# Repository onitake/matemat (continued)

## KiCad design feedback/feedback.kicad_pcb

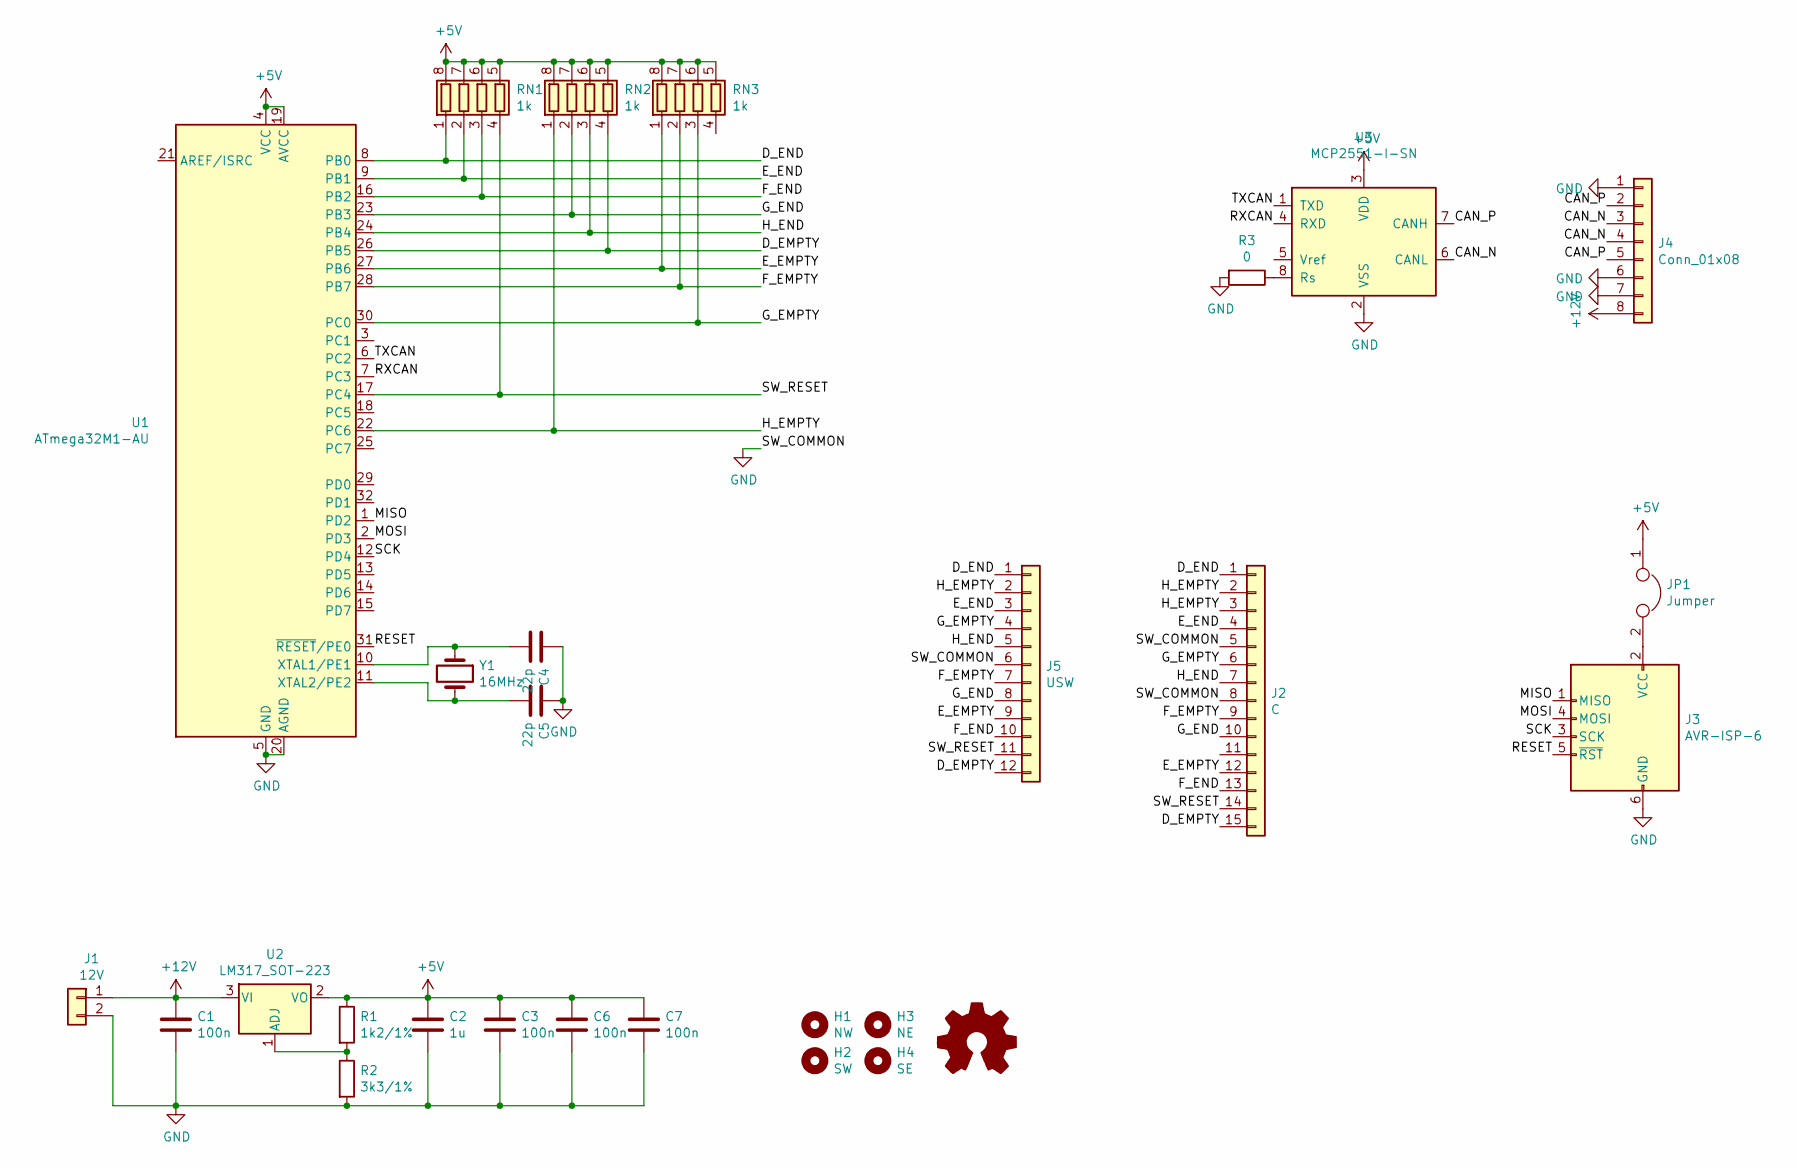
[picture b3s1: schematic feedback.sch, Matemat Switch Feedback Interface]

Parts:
C1, C3, C6, C7: 100n; C_0805_2012Metric_Pad1.15x1.40mm_HandSolder
C2: 1u; C_0805_2012Metric_Pad1.15x1.40mm_HandSolder
C4, C5: 22p; C_0805_2012Metric_Pad1.15x1.40mm_HandSolder
H1: NW; MountingHole_3.2mm_M3_ISO7380
H2: SW; MountingHole_3.2mm_M3_ISO7380
H3: NE; MountingHole_3.2mm_M3_ISO7380
H4: SE; MountingHole_3.2mm_M3_ISO7380
J1: 12V; TerminalBlock_TE_282834-2_1x02_P2.54mm_Horizontal
J2: C; Molex_MLX-42002_10-84-4150_3x5-Pin_P6.35mm_Vertical
J3: AVR-ISP-6; PinHeader_2x03_P2.54mm_Vertical
J4: Conn_01x08; TerminalBlock_TE_282834-8_1x08_P2.54mm_Horizontal
J5: USW; TerminalBlock_TE_1-282834-2_1x12_P2.54mm_Horizontal
JP1: Jumper; PinHeader_1x02_P2.54mm_Vertical
OHW1: Logo_Open_Hardware_Small; OSHW-Logo2_7.3x6mm_SilkScreen
R1: 1k2/1%; R_0805_2012Metric_Pad1.15x1.40mm_HandSolder
R2: 3k3/1%; R_0805_2012Metric_Pad1.15x1.40mm_HandSolder
R3: 0; R_0805_2012Metric_Pad1.15x1.40mm_HandSolder
RN1, RN2, RN3: 1k; R_Array_Convex_4x1206
U1: ATmega32M1-AU; TQFP-32_7x7mm_P0.8mm
U2: LM317_SOT-223; SOT-223-3_TabPin2
U3: MCP2551-I-SN; SOIC-8_3.9x4.9mm_P1.27mm
Y1: 16MHz; Crystal_SMD_HC49-SD

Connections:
+5V: C2.1, C3.1, C6.1, C7.1, JP1.1, R1.1, RN1.5 (R4.2), RN1.6 (R3.2), RN1.7 (R2.2), RN1.8 (R1.2), RN2.5 (R4.2), RN2.6 (R3.2), RN2.7 (R2.2), RN2.8 (R1.2), RN3.5 (R4.2), RN3.6 (R3.2), RN3.7 (R2.2), RN3.8 (R1.2), U1.4 (VCC), U1.19 (AVCC), U2.2 (VO), U3.3 (VDD)
+12V: C1.1, J1.1, J4.8, U2.3 (VI)
/CAN_N: J4.3, J4.4, U3.6 (CANL)
/CAN_P: J4.2, J4.5, U3.7 (CANH)
/D_EMPTY: J2.15, J5.12, RN2.4 (R4.1), U1.26 (PB5)
/D_END: J2.1, J5.1, RN1.1 (R1.1), U1.8 (PB0)
/E_EMPTY: J2.12, J5.9, RN3.1 (R1.1), U1.27 (PB6)
/E_END: J2.4, J5.3, RN1.2 (R2.1), U1.9 (PB1)
/F_EMPTY: J2.9, J5.7, RN3.2 (R2.1), U1.28 (PB7)
/F_END: J2.13, J5.10, RN1.3 (R3.1), U1.16 (PB2)
/G_EMPTY: J2.6, J5.4, RN3.3 (R3.1), U1.30 (PC0)
/G_END: J2.10, J5.8, RN2.2 (R2.1), U1.23 (PB3)
/H_EMPTY: J2.2, J2.3, J5.2, RN2.1 (R1.1), U1.22 (PC6)
/H_END: J2.7, J5.5, RN2.3 (R3.1), U1.24 (PB4)
/MISO: J3.1 (MISO), U1.1 (PD2)
/MOSI: J3.4 (MOSI), U1.2 (PD3)
/RESET: J3.5 (~RST), U1.31 (~RESET~/PE0)
/RXCAN: U1.7 (PC3), U3.4 (RXD)
/SCK: J3.3 (SCK), U1.12 (PD4)
/SW_RESET: J2.14, J5.11, RN1.4 (R4.1), U1.17 (PC4)
/TXCAN: U1.6 (PC2), U3.1 (TXD)
GND: C1.2, C2.2, C3.2, C4.1, C5.1, C6.2, C7.2, J1.2, J2.5, J2.8, J3.6 (GND), J4.1, J4.6, J4.7, J5.6, R2.2, R3.2, U1.5 (GND), U1.20 (AGND), U3.2 (VSS)
unnamed: C4.2, U1.10 (XTAL1/PE1), Y1.1
unnamed: C5.2, U1.11 (XTAL2/PE2), Y1.2
unnamed: J3.2 (VCC), JP1.2
unnamed: R1.2, R2.1, U2.1 (ADJ)
unnamed: R3.1, U3.8 (Rs)

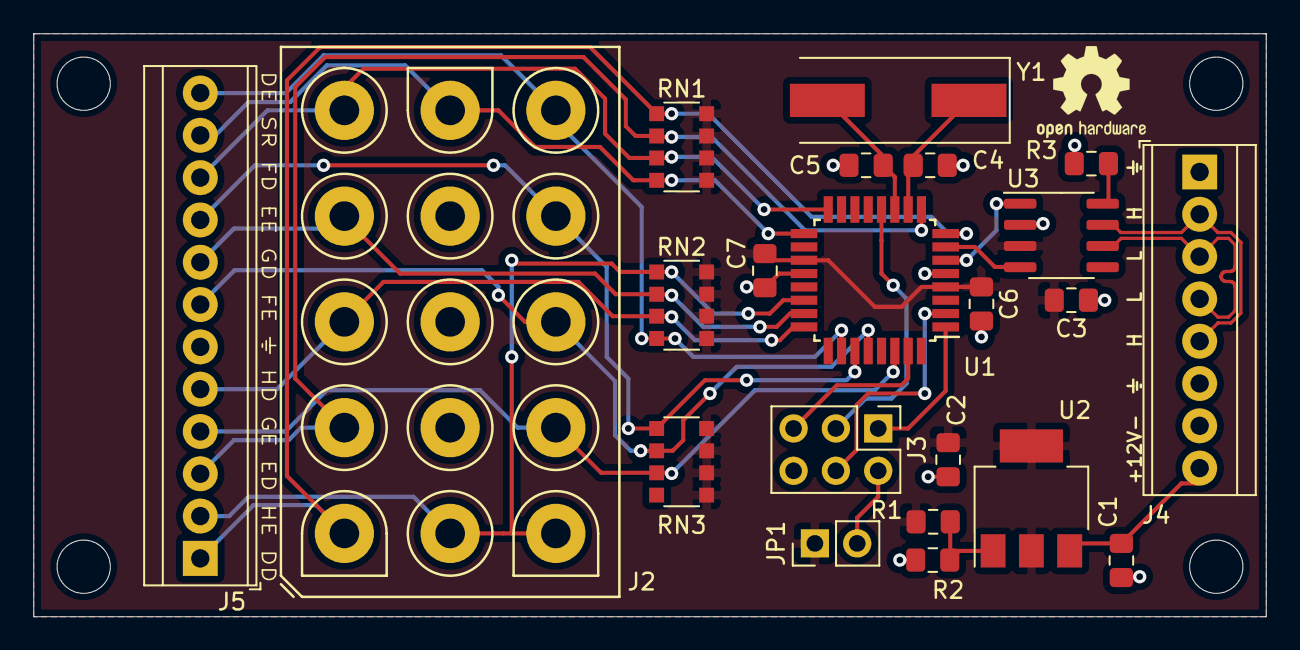
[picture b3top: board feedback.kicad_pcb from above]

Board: 2 copper layers, 74.0 x 35.0 mm, 27 parts (0 on the bottom side), 27 nets.

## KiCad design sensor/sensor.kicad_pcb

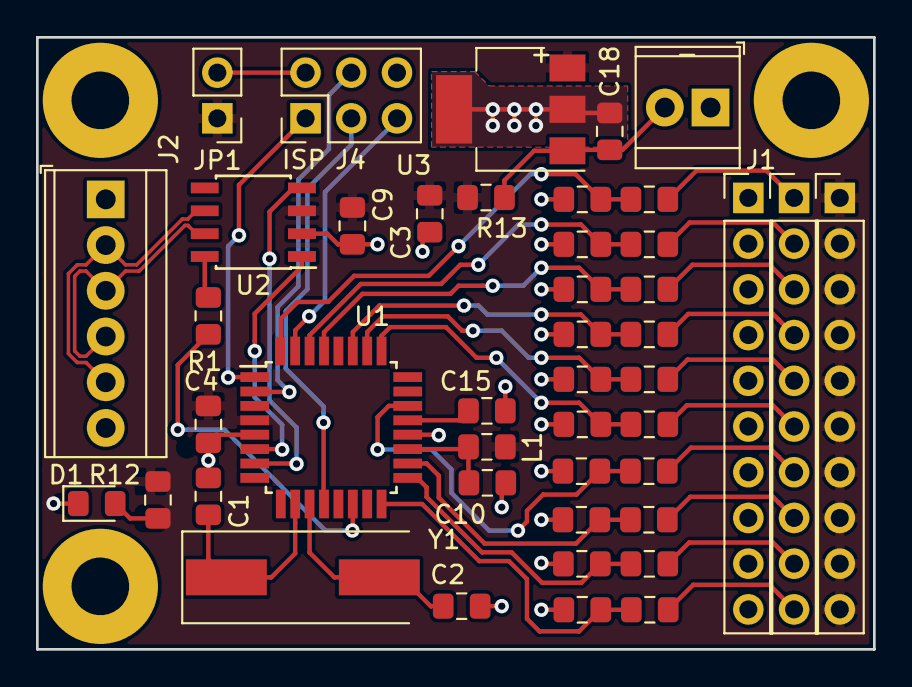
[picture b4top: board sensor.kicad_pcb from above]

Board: 2 copper layers, 46.5 x 34.0 mm, 47 parts (0 on the bottom side), 39 nets.

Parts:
C1, C2: 22p; C_0805_2012Metric_Pad1.15x1.40mm_HandSolder
C3: 10u; C_0805_2012Metric_Pad1.15x1.40mm_HandSolder
C4, C9, C10, C18: 100n; C_0805_2012Metric_Pad1.15x1.40mm_HandSolder
C5, C6, C7, C8, C11, C12, C13, C14, C16, C17: 10n; C_0805_2012Metric_Pad1.15x1.40mm_HandSolder
C15: 100n/0R; C_0805_2012Metric_Pad1.15x1.40mm_HandSolder
D1: POWER; LED_0805_2012Metric_Pad1.15x1.40mm_HandSolder
H1: NW; MountingHole_3.2mm_M3_Pad
H2: NE; MountingHole_3.2mm_M3_Pad
H3: SW; MountingHole_3.2mm_M3_Pad
J1: 12V; TerminalBlock_TE_282834-2_1x02_P2.54mm_Horizontal
J2: CAN; TerminalBlock_TE_282834-6_1x06_P2.54mm_Horizontal
J4: AVR-ISP-6; PinHeader_2x03_P2.54mm_Vertical
J5: SENSOR IN; PinHeader_1x10_P2.54mm_Vertical
J6: SENSOR VCC; PinHeader_1x10_P2.54mm_Vertical
J7: SENSOR GND; PinHeader_1x10_P2.54mm_Vertical
JP1: ISP POWER; PinHeader_1x02_P2.54mm_Vertical
L1: 10u; L_0805_2012Metric_Pad1.15x1.40mm_HandSolder
R1, R2, R3, R4, R5, R6, R7, R8, R9, R10, R11: 0; R_0805_2012Metric_Pad1.15x1.40mm_HandSolder
R12: 470; R_0805_2012Metric_Pad1.15x1.40mm_HandSolder
R13: DNP/0; R_0805_2012Metric_Pad1.15x1.40mm_HandSolder
U1: ATmega32M1-AU; TQFP-32_7x7mm_P0.8mm
U2: MCP2551-I-SN; SOIC-8_3.9x4.9mm_P1.27mm
U3: LM2937xMP; SOT-223-3_TabPin2
Y1: 16MHz; Crystal_SMD_HC49-SD

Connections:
/ADC5: C8.1, R5.2, U1.16
/ADC8: C7.1, R4.2, U1.17
/ADC9: C6.1, R3.2, U1.18
/ADC10: C5.1, R2.2, U1.22
/AIN0: J5.7, R2.1
/AIN1: J5.8, R3.1
/AIN2: J5.9, R4.1
/AIN3: J5.10, R5.1
/AREF: C15.1, U1.21
/CAN_HISPEED: R1.2, U1.14
/CAN_N: J2.2, J2.5, U2.6
/CAN_P: J2.3, J2.4, U2.7
/CAN_RXD: U1.7, U2.4
/CAN_TXD: U1.6, U2.1
/DIN0: J5.1, R6.1
/DIN1: J5.2, R7.1
/DIN2: J5.3, R8.1
/DIN3: J5.4, R9.1
/DIN4: J5.5, R10.1
/DIN5: J5.6, R11.1
/ISP_MISO: J4.1, U1.1
/ISP_MOSI: J4.4, U1.2
/ISP_SCK: J4.3, U1.12
/PCINT5: C16.1, R10.2, U1.26
/PCINT6: C14.1, R9.2, U1.27
/PCINT8: C12.1, R7.2, U1.30
/PCINT15: C17.1, R11.2, U1.25
/PCINT16: C13.1, R8.2, U1.29
/PCINT17: C11.1, R6.2, U1.32
/~ISP_RESET: J4.5, U1.31
GND: C1.2, C2.1, C3.2, C4.2, C5.2, C6.2, C7.2, C8.2, C9.2, C10.2, C11.2, C12.2, C13.2, C14.2, C15.2, C16.2, C17.2, C18.2, D1.1, H1.1, H2.1, H3.1, J1.1, J2.1, J2.6, J4.6, J7.1, J7.2, J7.3, J7.4, J7.5, J7.6, J7.7, J7.8, J7.9, J7.10, U1.5, U1.20, U2.2, U3.2
unnamed: C1.1, U1.10, Y1.1
unnamed: C2.2, U1.11, Y1.2
unnamed: C18.1, J1.2, R13.2, U3.1
unnamed: D1.2, R12.1
unnamed: J4.2, JP1.2
unnamed: R1.1, U2.8
VAA: C10.1, L1.2, U1.19
VCC: C3.1, C4.1, C9.1, J6.1, J6.2, J6.3, J6.4, J6.5, J6.6, J6.7, J6.8, J6.9, J6.10, JP1.1, L1.1, R12.2, R13.1, U1.4, U2.3, U3.3

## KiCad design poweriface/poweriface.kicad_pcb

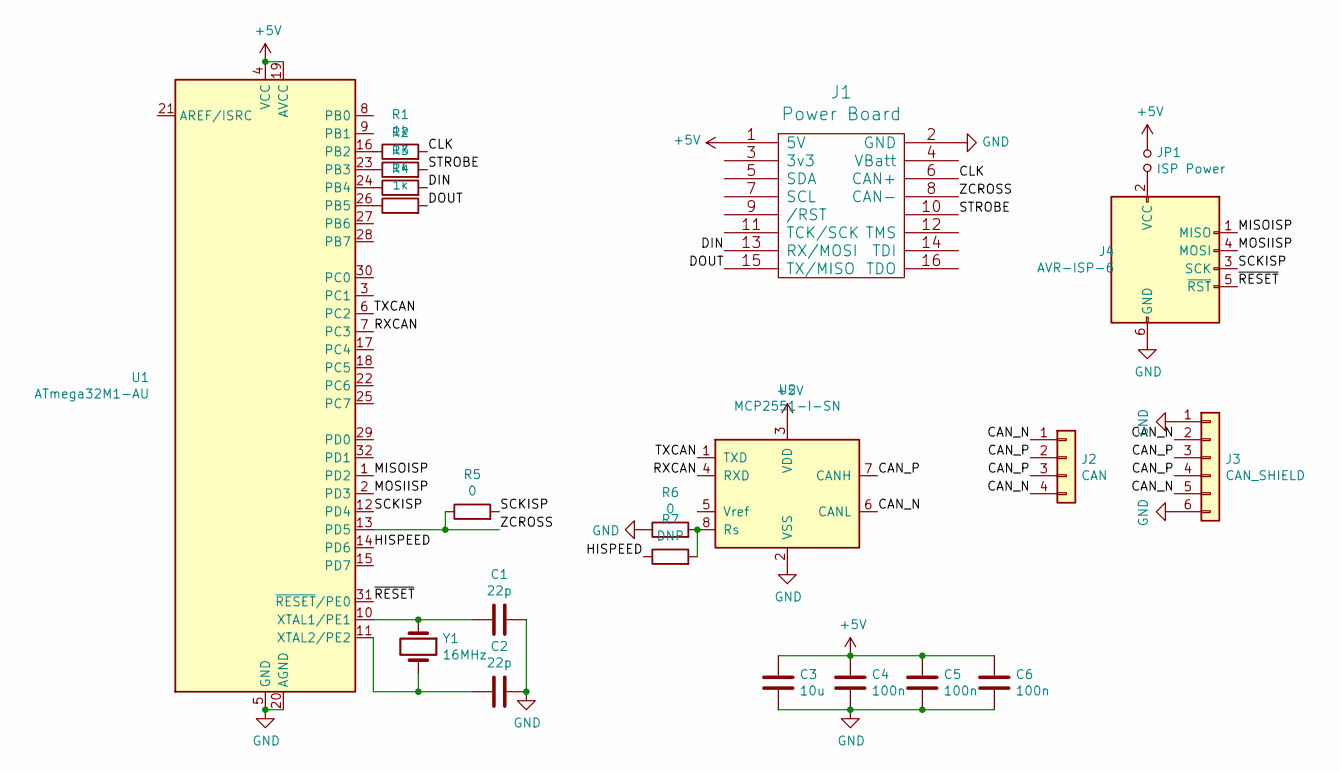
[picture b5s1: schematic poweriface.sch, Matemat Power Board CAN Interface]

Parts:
C1, C2: 22p; C_0805_2012Metric_Pad1.15x1.40mm_HandSolder
C3: 10u; C_0805_2012Metric_Pad1.15x1.40mm_HandSolder
C4, C5, C6: 100n; C_0805_2012Metric_Pad1.15x1.40mm_HandSolder
J1: Power Board; PinSocket_2x08_P2.54mm_Vertical
J2: CAN; TerminalBlock_TE_282834-4_1x04_P2.54mm_Horizontal
J3: CAN_SHIELD; TerminalBlock_TE_282834-6_1x06_P2.54mm_Horizontal
J4: AVR-ISP-6; PinHeader_2x03_P2.54mm_Vertical
JP1: ISP Power; PinHeader_1x02_P2.54mm_Vertical
R1, R2, R3, R4: 1k; R_0805_2012Metric_Pad1.15x1.40mm_HandSolder
R5, R6: 0; R_0805_2012Metric_Pad1.15x1.40mm_HandSolder
R7: DNP; R_0805_2012Metric_Pad1.15x1.40mm_HandSolder
U1: ATmega32M1-AU; TQFP-32_7x7mm_P0.8mm
U2: MCP2551-I-SN; SOIC-8_3.9x4.9mm_P1.27mm
Y1: 16MHz; Crystal_SMD_HC49-SD

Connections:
+5V: C3.1, C4.1, C5.1, C6.1, J1.1 (5V), JP1.1, U1.4 (VCC), U1.19 (AVCC), U2.3 (VDD)
/CAN_N: J2.1, J2.4, J3.2, J3.5, U2.6 (CANL)
/CAN_P: J2.2, J2.3, J3.3, J3.4, U2.7 (CANH)
/CLK: J1.6 (CAN+), R1.2
/DIN: J1.13 (RX/MOSI), R3.2
/DOUT: J1.15 (TX/MISO), R4.2
/HISPEED: R7.1, U1.14 (PD6)
/MISOISP: J4.1 (MISO), U1.1 (PD2)
/MOSIISP: J4.4 (MOSI), U1.2 (PD3)
/RXCAN: U1.7 (PC3), U2.4 (RXD)
/SCKISP: J4.3 (SCK), R5.2, U1.12 (PD4)
/STROBE: J1.10, R2.2
/TXCAN: U1.6 (PC2), U2.1 (TXD)
/ZCROSS: J1.8 (CAN-), R5.1, U1.13 (PD5)
/~RESET: J4.5 (~RST), U1.31 (~RESET~/PE0)
GND: C1.1, C2.1, C3.2, C4.2, C5.2, C6.2, J1.2 (GND), J3.1, J3.6, J4.6 (GND), R6.1, U1.5 (GND), U1.20 (AGND), U2.2 (VSS)
unnamed: C1.2, U1.10 (XTAL1/PE1), Y1.1
unnamed: C2.2, U1.11 (XTAL2/PE2), Y1.2
unnamed: J4.2 (VCC), JP1.2
unnamed: R1.1, U1.16 (PB2)
unnamed: R2.1, U1.23 (PB3)
unnamed: R3.1, U1.24 (PB4)
unnamed: R4.1, U1.26 (PB5)
unnamed: R6.2, R7.2, U2.8 (Rs)

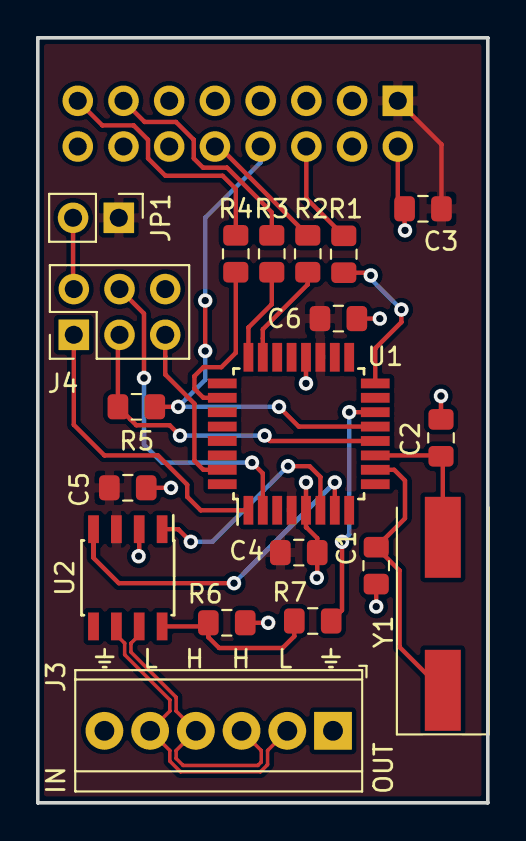
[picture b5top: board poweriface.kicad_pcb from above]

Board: 2 copper layers, 25.0 x 42.5 mm, 20 parts (1 on the bottom side), 24 nets.

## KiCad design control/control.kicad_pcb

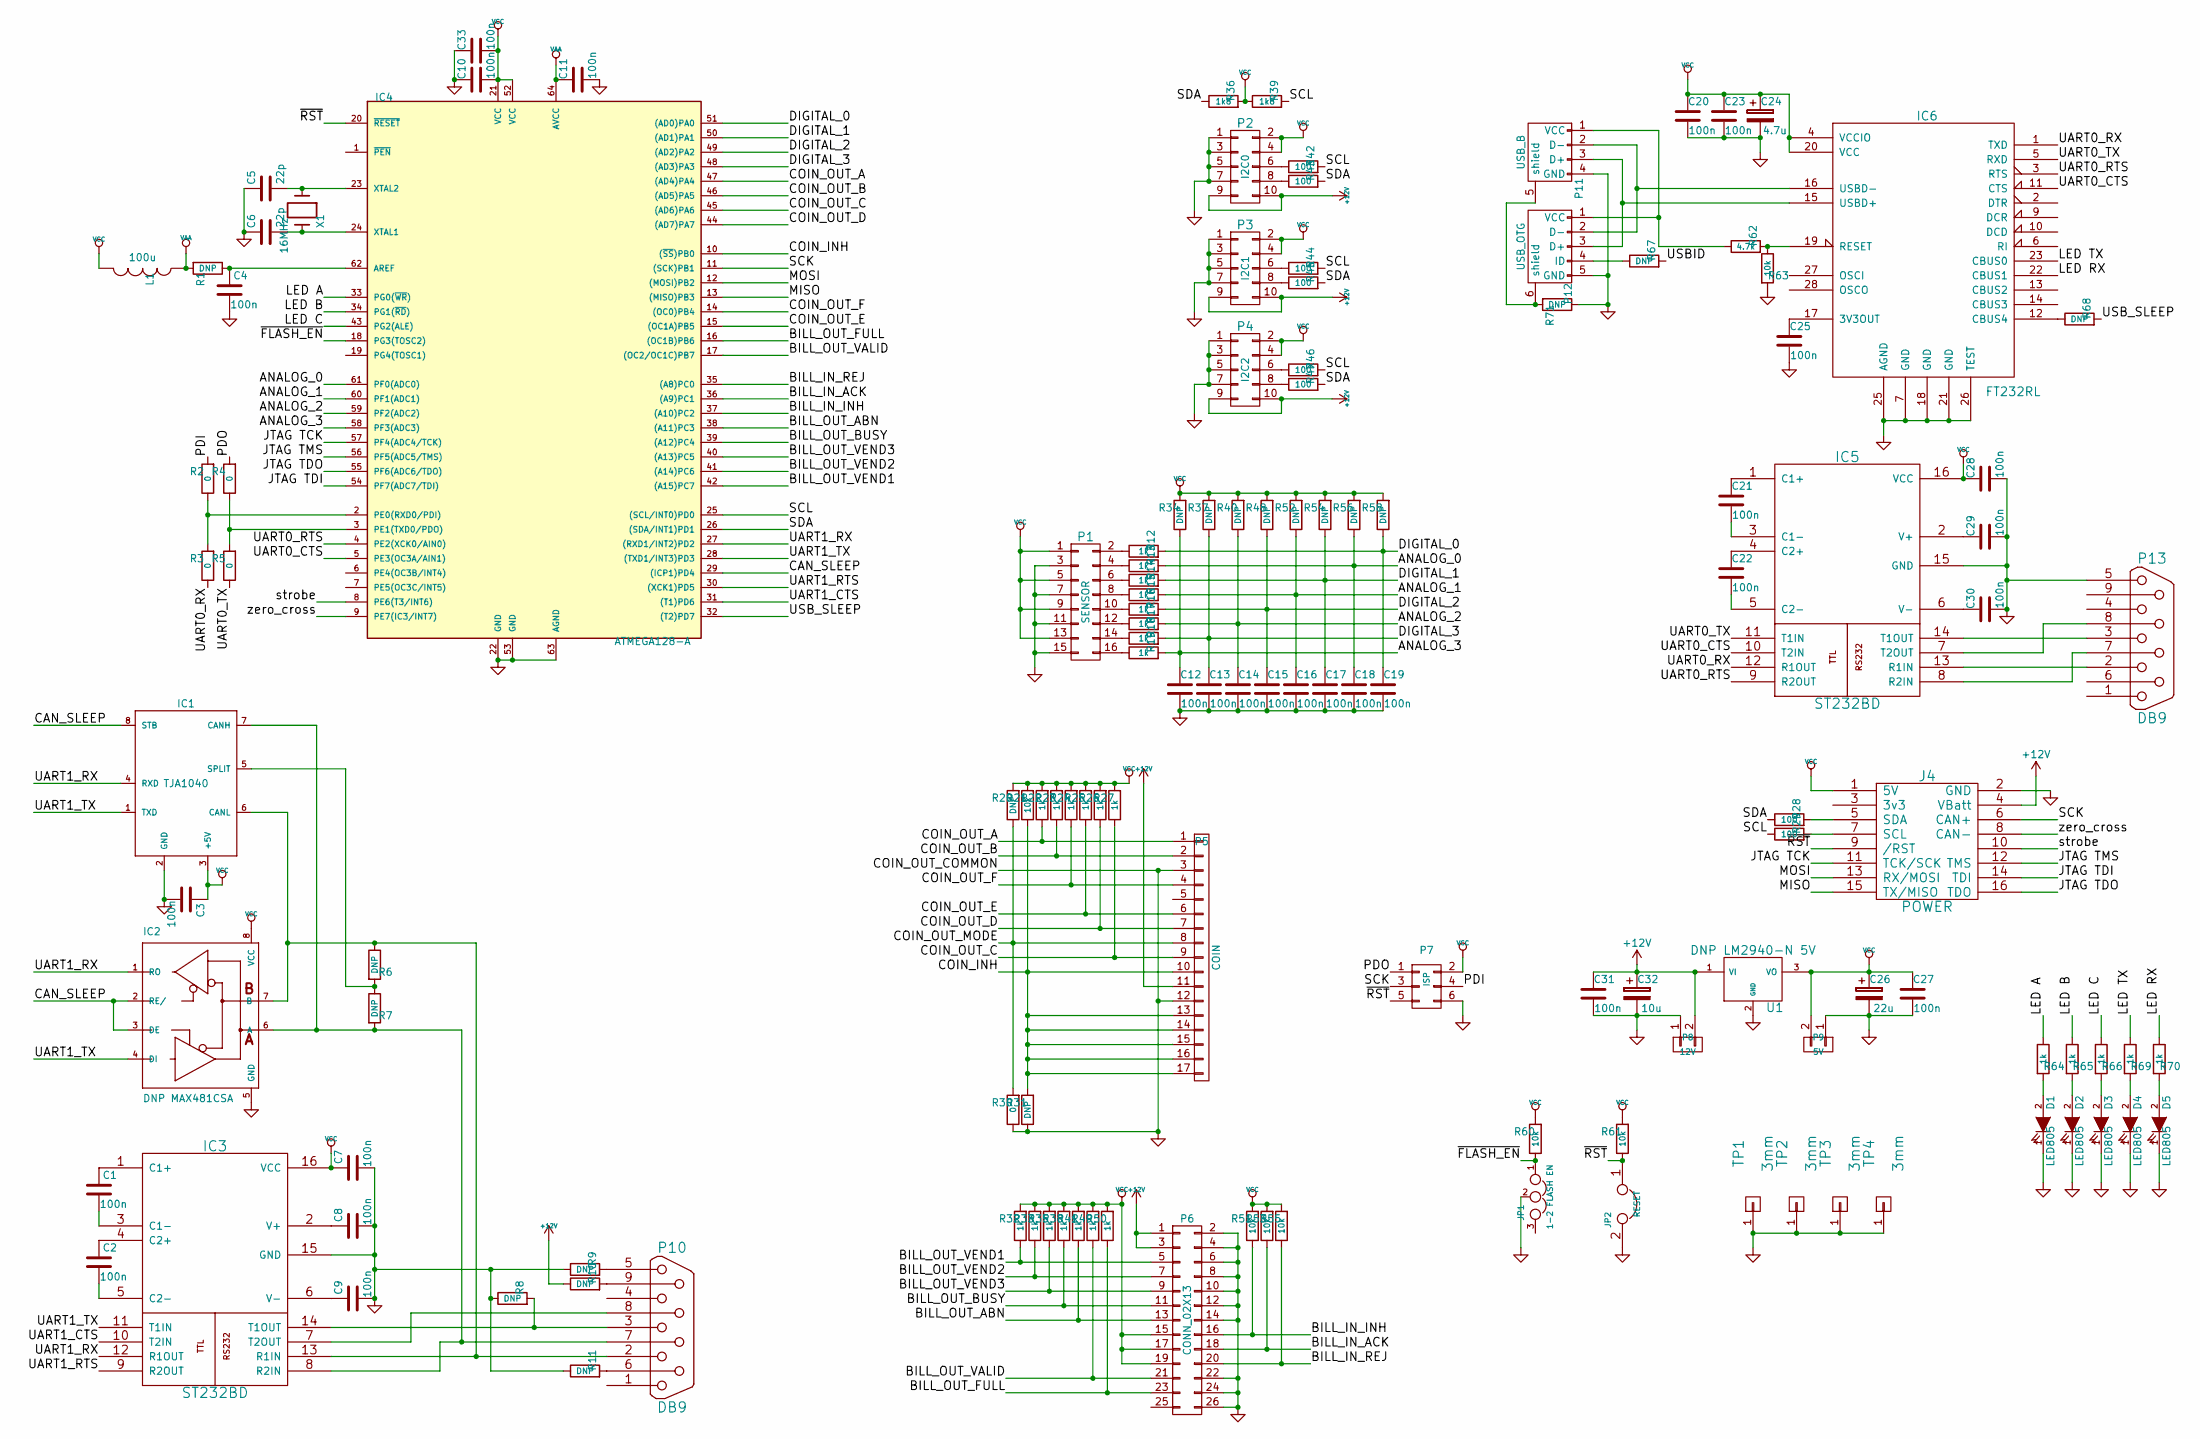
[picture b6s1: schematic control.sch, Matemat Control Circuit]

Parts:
C1, C2, C3, C4, C7, C8, C9, C10, C11, C12, C13, C14, C15, C16, C17, C18, C19, C20, C21, C22, C23, C25, C27, C28, C29, C30, C31, C33: 100n; C_0805_HandSoldering
C5, C6: 22p; C_0805_HandSoldering
C24: 4.7u; C_Radial_D5_L11_P2.5
C26: 22u; C_Radial_D5_L11_P2.5
C32: 10u; C_Radial_D5_L11_P2.5
D1, D2, D3, D4, D5: LED805; LED-0805
IC1: TJA1040; SOIC-8_3.9x4.9mm_Pitch1.27mm
IC2: DNP MAX481CSA; SOIC-8_3.9x4.9mm_Pitch1.27mm
IC3, IC5: ST232BD; SOIC-16_3.9x9.9mm_Pitch1.27mm
IC4: ATMEGA128-A; TQFP-64_14x14mm_Pitch0.8mm
IC6: FT232RL; SSOP-28_5.3x10.2mm_Pitch0.65mm
J4: POWER; Pin_Header_Straight_2x08
JP1: 1-2 FLASH EN; Pin_Header_Straight_1x03
JP2: RESET; Pin_Header_Straight_1x02
L1: 100u; wuerth_elektronik_v5-WE-PD2_S
P1: SENSOR; Pin_Header_Straight_2x08
P2: I2C0; Pin_Header_Straight_2x05
P3: I2C1; Pin_Header_Straight_2x05
P4: I2C2; Pin_Header_Straight_2x05
P5: COIN; Pin_Header_Straight_1x17
P6: CONN_02X13; Pin_Header_Straight_2x13
P7: ISP; Pin_Header_Straight_2x03
P8: 12V; Bornier_B2_Phoenix
P9: 5V; Bornier_B2_Phoenix
P10, P13: DB9; DB9MCS
P11: USB_B
P12: USB_OTG; USB_Micro-B
R1, R6, R7, R8, R9, R10, R11, R20, R31, R34, R37, R40, R48, R52, R54, R56, R58, R67, R68, R71: DNP; R_0805_HandSoldering
R2, R3, R4, R5, R30: 0; R_0805_HandSoldering
R12, R13, R14, R15, R16, R17, R18, R19, R22, R23, R24, R25, R26, R27, R32, R33, R35, R38, R41, R49, R50, R64, R65, R66, R69, R70: 1k; R_0805_HandSoldering
R21, R51, R53, R55, R60, R61, R63: 10k; R_0805_HandSoldering
R28, R29, R42, R43, R44, R45, R46, R47: 100; R_0805_HandSoldering
R36, R39: 1k8; R_0805_HandSoldering
R62: 4.7k; R_0805_HandSoldering
TP1, TP2, TP3, TP4: 3mm; MountingHole_3mm
U1: DNP LM2940-N 5V; SOT-223
X1: 16MHz; Q_49U3HMS

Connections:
+12V: C31.1, C32.1, J4.4 (VBatt), P2.9, P2.10, P3.9, P3.10, P4.9, P4.10, P5.11, P6.1, P6.3, P8.2, R10.1, U1.1 (VI)
/ANALOG_0: C18.1, IC4.61 (PF0(ADC0)), R13.2, R56.1
/ANALOG_1: C16.1, IC4.60 (PF1(ADC1)), R15.2, R52.1
/ANALOG_2: C14.1, IC4.59 (PF2(ADC2)), R17.2, R40.1
/ANALOG_3: C12.1, IC4.58 (PF3(ADC3)), R19.2, R34.1
/BILL_IN_ACK: IC4.36 ((A9)PC1), P6.18, R53.1
/BILL_IN_INH: IC4.37 ((A10)PC2), P6.16, R51.1
/BILL_IN_REJ: IC4.35 ((A8)PC0), P6.20, R55.1
/BILL_OUT_ABN: IC4.38 ((A11)PC3), P6.13, R41.1
/BILL_OUT_BUSY: IC4.39 ((A12)PC4), P6.11, R38.1
/BILL_OUT_FULL: IC4.16 ((OC1B)PB6), P6.23, R50.1
/BILL_OUT_VALID: IC4.17 ((OC2/OC1C)PB7), P6.21, R49.1
/BILL_OUT_VEND1: IC4.42 ((A15)PC7), P6.5, R32.1
/BILL_OUT_VEND2: IC4.41 ((A14)PC6), P6.7, R33.1
/BILL_OUT_VEND3: IC4.40 ((A13)PC5), P6.9, R35.1
/CAN_SLEEP: IC1.8 (STB), IC2.2 (RE/), IC2.3 (DE), IC4.29 ((ICP1)PD4)
/COIN_INH: IC4.10 ((~SS~)PB0), P5.10, P5.13, P5.14, P5.15, P5.16, P5.17, R21.1, R31.2
/COIN_OUT_A: IC4.47 ((AD4)PA4), P5.1, R22.1
/COIN_OUT_B: IC4.46 ((AD5)PA5), P5.2, R23.1
/COIN_OUT_C: IC4.45 ((AD6)PA6), P5.9, R27.1
/COIN_OUT_D: IC4.44 ((AD7)PA7), P5.7, R26.1
/COIN_OUT_E: IC4.15 ((OC1A)PB5), P5.6, R25.1
/COIN_OUT_F: IC4.14 ((OC0)PB4), P5.4, R24.1
/COIN_OUT_MODE: P5.8, R20.1, R30.2
/DIGITAL_0: C19.1, IC4.51 ((AD0)PA0), R12.2, R58.1
/DIGITAL_1: C17.1, IC4.50 ((AD1)PA1), R14.2, R54.1
/DIGITAL_2: C15.1, IC4.49 ((AD2)PA2), R16.2, R48.1
/DIGITAL_3: C13.1, IC4.48 ((AD3)PA3), R18.2, R37.1
/JTAG TCK: IC4.57 (PF4(ADC4/TCK)), J4.11 (TCK/SCK)
/JTAG TDI: IC4.54 (PF7(ADC7/TDI)), J4.14 (TDI)
/JTAG TDO: IC4.55 (PF6(ADC6/TDO)), J4.16 (TDO)
/JTAG TMS: IC4.56 (PF5(ADC5/TMS)), J4.12 (TMS)
/LED A: IC4.33 (PG0(~WR~)), R64.1
/LED B: IC4.34 (PG1(~RD~)), R65.1
/LED C: IC4.43 (PG2(ALE)), R66.1
/LED RX: IC6.22 (CBUS1), R70.1
/LED TX: IC6.23 (CBUS0), R69.1
/MISO: IC4.13 ((MISO)PB3), J4.15 (TX/MISO)
/MOSI: IC4.12 ((MOSI)PB2), J4.13 (RX/MOSI)
/PDI: P7.4, R2.2
/PDO: P7.1, R4.2
/SCK: IC4.11 ((SCK)PB1), J4.6 (CAN+), P7.3
/SCL: IC4.25 ((SCL/INT0)PD0), R29.1, R39.2, R42.2, R44.2, R46.2
/SDA: IC4.26 ((SDA/INT1)PD1), R28.1, R36.1, R43.2, R45.2, R47.2
/UART0_CTS: IC4.5 (PE3(OC3A/AIN1)), IC5.10 (T2IN), IC6.11 (CTS)
/UART0_RTS: IC4.4 (PE2(XCK0/AIN0)), IC5.9 (R2OUT), IC6.3 (RTS)
/UART0_RX: IC5.12 (R1OUT), IC6.1 (TXD), R3.1
/UART0_TX: IC5.11 (T1IN), IC6.5 (RXD), R5.1
/UART1_CTS: IC3.10 (T2IN), IC4.31 ((T1)PD6)
/UART1_RTS: IC3.9 (R2OUT), IC4.30 ((XCK1)PD5)
/UART1_RX: IC1.4 (RXD), IC2.1 (RO), IC3.12 (R1OUT), IC4.27 ((RXD1/INT2)PD2)
/UART1_TX: IC1.1 (TXD), IC2.4 (DI), IC3.11 (T1IN), IC4.28 ((TXD1/INT3)PD3)
/USBID: R67.2
/USB_SLEEP: IC4.32 ((T2)PD7), R68.2
/strobe: IC4.8 (PE6(T3/INT6)), J4.10
/zero_cross: IC4.9 (PE7(IC3/INT7)), J4.8 (CAN-)
/~FLASH_EN~: IC4.18 (PG3(TOSC2)), JP1.1, R60.1
/~RST~: IC4.20 (~RESET), J4.9 (/RST), JP2.1, P7.5, R61.1
GND: C3.2, C4.2, C5.1, C6.1, C7.2, C8.2, C9.2, C10.1, C11.2, C12.2, C13.2, C14.2, C15.2, C16.2, C17.2, C18.2, C19.2, C20.2, C23.2, C24.2, C25.2, C26.2, C27.2, C28.2, C29.2, C30.2, C31.2, C32.2, C33.1, D1.1 (K), D2.1 (K), D3.1 (K), D4.1 (K), D5.1 (K), IC1.2 (GND), IC2.5 (GND), IC3.15 (GND), IC4.22 (GND), IC4.53 (GND), IC4.63 (AGND), IC5.15 (GND), IC6.7 (GND), IC6.18 (GND), IC6.21 (GND), IC6.25 (AGND), IC6.26 (TEST), J4.2 (GND), JP1.2, JP2.2, P1.3, P1.7, P1.11, P1.15, P2.1, P2.3, P2.5, P2.7, P3.1, P3.3, P3.5, P3.7, P4.1, P4.3, P4.5, P4.7, P5.3, P5.12, P6.2, P6.4, P6.6, P6.8, P6.10, P6.12, P6.14, P6.22, P6.24, P6.26, P7.6, P8.1, P9.1, P11.4 (GND), P12.5 (GND), P13.5, R8.1, R9.1, R11.1, R30.1, R31.1, R63.2, R71.1, TP1.1, TP2.1, TP3.1, TP4.1, U1.2 (GND)
unnamed: C1.1, IC3.1 (C1+)
unnamed: C1.2, IC3.3 (C1-)
unnamed: C2.1, IC3.4 (C2+)
unnamed: C2.2, IC3.5 (C2-)
unnamed: C4.1, IC4.62 (AREF), R1.1
unnamed: C5.2, IC4.23 (XTAL2), X1.1
unnamed: C6.2, IC4.24 (XTAL1), X1.2
unnamed: C8.1, IC3.2 (V+)
unnamed: C9.1, IC3.6 (V-)
unnamed: C21.1, IC5.1 (C1+)
unnamed: C21.2, IC5.3 (C1-)
unnamed: C22.1, IC5.4 (C2+)
unnamed: C22.2, IC5.5 (C2-)
unnamed: C25.1, IC6.17 (3V3OUT)
unnamed: C29.1, IC5.2 (V+)
unnamed: C30.1, IC5.6 (V-)
unnamed: D1.2 (A), R64.2
unnamed: D2.2 (A), R65.2
unnamed: D3.2 (A), R66.2
unnamed: D4.2 (A), R69.2
unnamed: D5.2 (A), R70.2
unnamed: IC1.5 (SPLIT), R6.2, R7.1
unnamed: IC1.6 (CANL), IC2.7 (B), IC3.13 (R1IN), P10.2, R6.1
unnamed: IC1.7 (CANH), IC2.6 (A), IC3.8 (R2IN), P10.7, R7.2
unnamed: IC3.7 (T2OUT), P10.8
unnamed: IC3.14 (T1OUT), P10.3, R8.2
unnamed: IC4.2 (PE0(RXD0/PDI)), R2.1, R3.2
unnamed: IC4.3 (PE1(TXD0/PDO)), R4.1, R5.2
unnamed: IC5.7 (T2OUT), P13.8
unnamed: IC5.8 (R2IN), P13.7
unnamed: IC5.13 (R1IN), P13.2
unnamed: IC5.14 (T1OUT), P13.3
unnamed: IC6.12 (CBUS4), R68.1
unnamed: IC6.15 (USBD+), P11.3 (D+), P12.3 (D+)
unnamed: IC6.16 (USBD-), P11.2 (D-), P12.2 (D-)
unnamed: IC6.19 (RESET), R62.2, R63.1
unnamed: J4.5 (SDA), R28.2
unnamed: J4.7 (SCL), R29.2
unnamed: P1.2, R12.1
unnamed: P1.4, R13.1
unnamed: P1.6, R14.1
unnamed: P1.8, R15.1
unnamed: P1.10, R16.1
unnamed: P1.12, R17.1
unnamed: P1.14, R18.1
unnamed: P1.16, R19.1
unnamed: P2.6, R42.1
unnamed: P2.8, R43.1
unnamed: P3.6, R44.1
unnamed: P3.8, R45.1
unnamed: P4.6, R46.1
unnamed: P4.8, R47.1
unnamed: P10.5, R9.2
unnamed: P10.6, R11.2
unnamed: P10.9, R10.2
unnamed: P11.1 (VCC), P12.1 (VCC), R62.1
unnamed: P11.5 (shield), P12.6 (shield), R71.2
unnamed: P12.4 (ID), R67.1
VAA: C11.1, IC4.64 (AVCC), L1.1, R1.2
VCC: C3.1, C7.1, C10.2, C20.1, C23.1, C24.1, C26.1, C27.1, C28.1, C33.2, IC1.3 (+5V), IC2.8 (VCC), IC3.16 (VCC), IC4.21 (VCC), IC4.52 (VCC), IC5.16 (VCC), IC6.4 (VCCIO), IC6.20 (VCC), J4.1 (5V), L1.2, P1.1, P1.5, P1.9, P1.13, P2.2, P2.4, P3.2, P3.4, P4.2, P4.4, P6.15, P6.17, P6.19, P7.2, P9.2, R20.2, R21.2, R22.2, R23.2, R24.2, R25.2, R26.2, R27.2, R32.2, R33.2, R34.2, R35.2, R36.2, R37.2, R38.2, R39.1, R40.2, R41.2, R48.2, R49.2, R50.2, R51.2, R52.2, R53.2, R54.2, R55.2, R56.2, R58.2, R60.2, R61.2, U1.3 (VO)

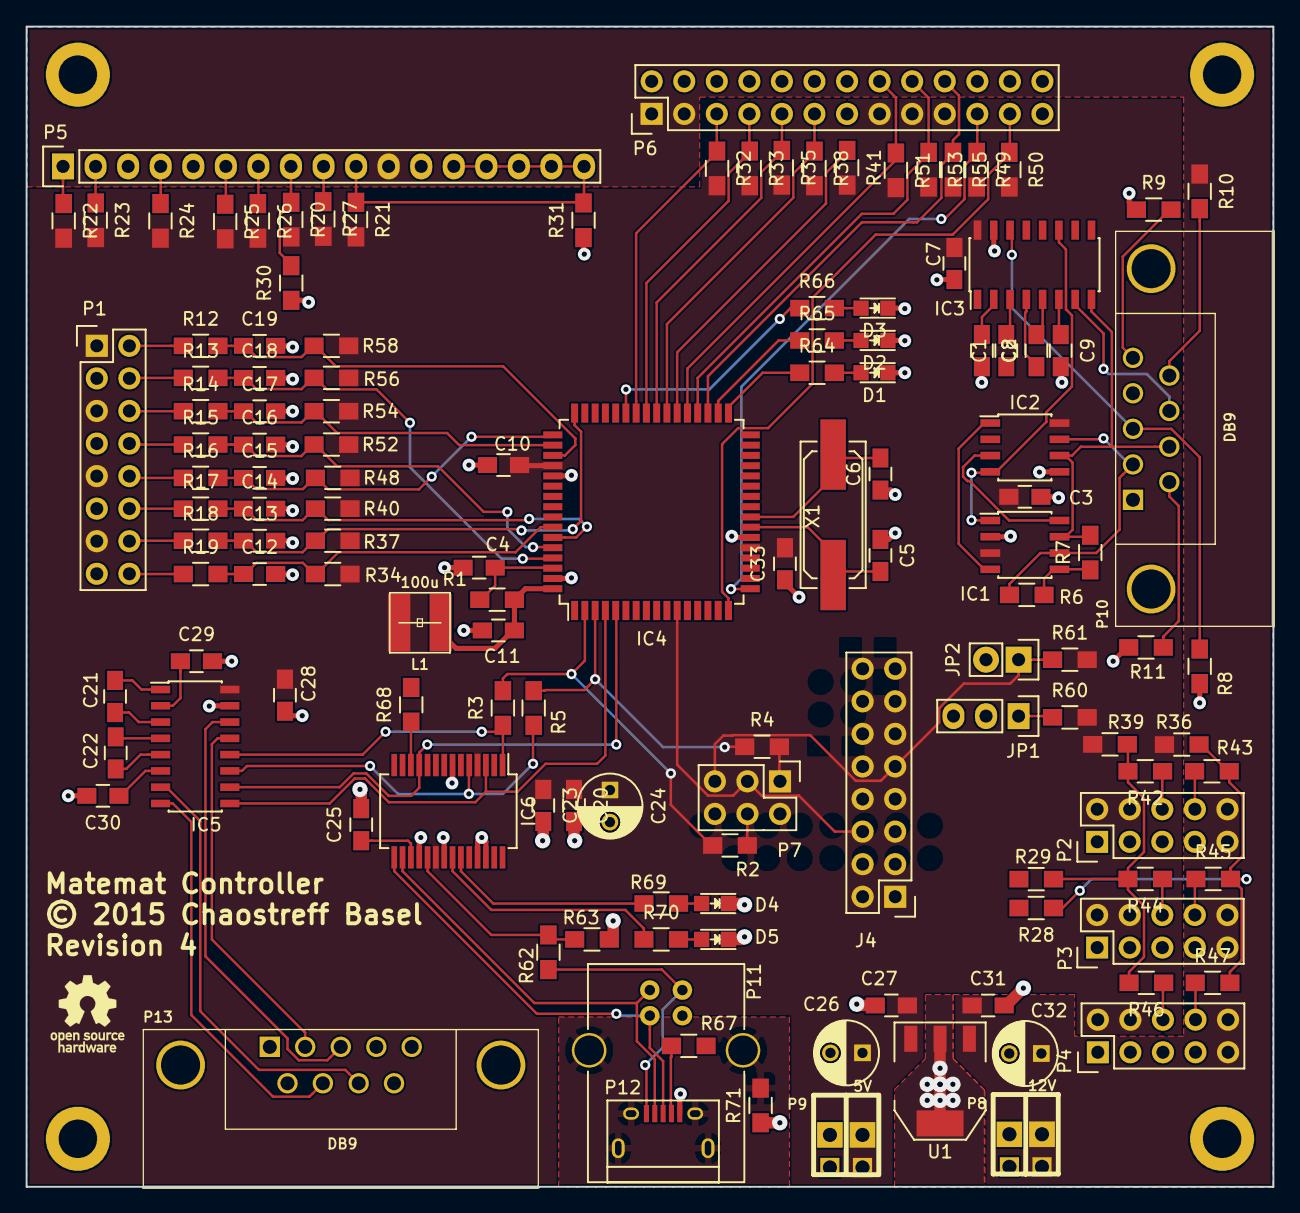
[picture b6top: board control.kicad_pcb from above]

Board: 2 copper layers, 97.2 x 90.5 mm, 136 parts (0 on the bottom side), 118 nets.

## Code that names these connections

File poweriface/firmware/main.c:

#include <inttypes.h>
#include <stdbool.h>
#include <avr/io.h>
#include <avr/interrupt.h>
#include <util/delay.h>
#include <can.h>
#include <messages.h>

static bool report_change = false;

static void init() {
	// Enable GPIO: PB2, PB3, PB4 output, low; PB5 input, pull-up on
 	PORTB = (PORTB & ~(_BV(PB2) | _BV(PB3) | _BV(PB4))) | _BV(PB5);
	DDRB = (DDRB & ~_BV(PB5)) | (_BV(PB2) | _BV(PB3) | _BV(PB4));
	
	// Initialize CAN interface
	can_init(BITRATE_125_KBPS);
	// Regular receive/transmit mode
	can_set_mode(NORMAL_MODE);

	// Filter for messages addressed to us (RTR on)
	can_filter_t us = {
		.id = CAN_HOSTID_POWER,
		.mask = CAN_HOSTID_MASK,
		.flags = {
			.rtr = 1,
			.extended = 0,
		},
	};
	can_set_filter(0, &us);
	// Filter for public messages (RTR off)
	can_filter_t pub = {
		.id = CAN_HOSTID_BROADCAST,
		.mask = CAN_HOSTID_MASK,
		.flags = {
			.rtr = 0,
			.extended = 0,
		},
	};
	can_set_filter(1, &pub);

	// Enable interrupts to start reception
	sei();
}


// UART bit-uart_bang 8 bits on the debug port, LSB first, 1 stop bit, no parity, 9600 baud
void uart_bang(uint8_t data) {
	// Start bit: low
	PORTB &= ~_BV(PB4);
	_delay_us(102);
	for (uint8_t i = 0; i < 8; i++) {
		// data bit
		if (data & (_BV(i))) {
			PORTB |= _BV(PB4);
		} else {
			PORTB &= ~_BV(PB4);
		}
		_delay_us(102);
	}
	// Stop bit: high (and stay there after)
	PORTB |= _BV(PB4);
	_delay_us(102);
}

// Bit-bang pattern (LSB first) out the data line
uint16_t bang(uint16_t data) {
	uint16_t in = 0;
	for (uint8_t i = 0; i < 16; i++) {
		// Data bit
		if (data & 1) {
			PORTB |= _BV(PB4);
		} else {
			PORTB &= ~_BV(PB4);
		}
		// Clock up
		PORTB |= _BV(PB2);
		_delay_us(4);
		// Clock down
		PORTB &= ~_BV(PB2);
		_delay_us(4);
		// Read
		if (PINB & _BV(PB5)) {
			in |= 1;
		}
		// Shift
		data >>= 1;
		in <<= 1;
	}
	// Clear data
	PORTB &= ~_BV(PB4);
	return in;
}

// Strobe output
void strobe() {
	// Strobe
	PORTB |= _BV(PB3);
	_delay_us(4);
	PORTB &= ~_BV(PB3);
}

static void send_status() {
	// Bit-bang register contents in (also send out zeros, but don't strobe)
	uint16_t status = bang(0);
	// Send the current state back out to prevent glitches
	bang(status);

	if (can_check_free_buffer()) {
		can_t msg = {
			.id = CAN_MSG_POWER_STATUS,
			.flags = {
				.rtr = 0,
			},
			.length = 2,
			.data = { (uint8_t) (status >> 8), (uint8_t) status, },
		};
		can_send_message(&msg);
	}
}

static void fire_relay(uint8_t num) {
	if (num == 0) {
		bang(0);
		strobe();
	} else if (num <= 5) {
		uint16_t out = 0x0080 >> (num - 1);
		bang(out);
		strobe();
	}
}

static void loop() {
	// Check for new messages
	if (can_check_message()) {
		can_t msg = { 0 };
		uint8_t status = can_get_message(&msg);
		if (status != 0) {
			switch (msg.id) {
			case CAN_MSG_POWER_STATUS:
				send_status();
				break;
			case CAN_MSG_POWER_DISPENSE:
				if (msg.length == 1) {
					// stop (d0 = 0) or fire relay (d0 = 1..5)
					fire_relay(msg.data[0]);
					// also send out the current status
					send_status();
				}
				break;
			case CAN_MSG_AUTO_STATUS:
				if (msg.length == 1) {
					report_change = msg.data[0] ? true : false;
				}
				break;
			}
		}
	}
}

int main() {
	init();
	while (1) {
		loop();
	}
}

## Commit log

2015-04-01 First prototype all-in-one schema
2015-04-01 Updated schema with more complete circuit
2015-04-01 Added datasheet URL for ATmega644P MCU
2015-04-01 Added zero crossing detector circuit simulation graph
2015-04-01 Added datasheet URL for BT136 Triac (NXP)
2015-04-01 Added KiCad library cache with missing parts
2015-04-02 Added redesigned control board schema and PCB layout
2015-04-02 Added board layout for smaller DB9 sockets
2015-04-02 Unified silk screen text sizes, fixed and relocated some text
2015-04-02 Fixed a number of errata in first control board revision Swapped USB B port D+ and D- lines Swapped UART0 RX and TX lines Changed resistor values Added UART0 RX and TX LEDs Conntected USB sleep contr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
2015-04-02 Added netlists to gitignore
2015-04-02 Added global KiCad project
2015-04-03 Updated large DB9 socket PCB with errata from schema
2015-04-03 Added ATmega128A data sheet Removed ATmega644P data sheet
2015-04-03 Added component library Updated conmponents in schematic Changed resistors and capacitors to standard symbol
2015-04-03 Fixed banknote scanner connector erratum, short circuit on power lines
2015-04-03 Updated schematic revision and copyright
2015-04-05 Added module library Fixed up schema with new part names Partial PCB redesign, incorporated schematic changes and errata Made PCB slightly smaller
2015-04-06 Updated gitignore
2015-04-06 Updated PCB Placed part labels Moved some parts to use space more efficiently
2015-04-06 Converted board to new KiCAD format
2015-04-06 Removed previous PCB layout
2015-04-06 Added -bak wildcard to gitignore
2015-04-06 Added copyright field and OSHW logo to PCB
2015-04-06 Removed separate data sheet references Added text file with data sheet URLs
2015-04-07 Added author list, readme and hardware license
2015-04-07 Updated data sheet list
2015-04-07 Removed PCB in old KiCAD format
2015-09-08 Moved circuit diagrams into separate directories Updated module library paths
2015-09-08 Added power board circuit diagrams and PCB design (sto)
2015-09-08 Added project file for old power board design
2015-09-08 Removed old power board circuit
2015-09-08 Added file cloning scripts for power board (sto)
2015-11-05 Updated control board for KiCad 4.0
2015-12-29 Removed pulldown resistors from analog/digital I/O block to save some space. Removed leftover reference from conversion to KiCad 4.
2015-12-30 Added new connection blocks for coin and banknote scanners
2015-12-30 Moved DB9 connectors in the schematic a little to clean up the trace mess
2015-12-30 Removed old coin and banknote connection block in schematic, rewired MCU for new block
2015-12-30 Added optional linear regulator for 5V Vcc. Replaced old connector symbols with current ones from the KiCad library.
2015-12-30 Added library backup files to git ignore list
2015-12-30 Updated layout with new/changed parts
2015-12-31 Added SOT-223 package to module library (currently missing from Debian)
2016-02-22 Corrected some typos and wording in readme
2019-04-01 WIP control board rewiring to make it smaller
2019-04-01 Update and cleanup for KiCAD 5
2019-04-01 Power board lib autocleanup
2019-04-01 Added more stuff to ignore list
2019-04-01 Updated power board for KiCAD 5
2019-04-01 Made board smaller and started rerouting
2019-04-01 Added recovered footprints back
2019-04-01 More rerouting
2019-04-03 Added CAN extension for power board
2019-04-04 Connected hispeed control to GPIO pin
2019-04-04 Fixed small power plane issues
2019-04-09 Updated annotations
2019-04-09 Replaced crystal footprint with less wasteful one
2019-04-13 Added CAN sensor board
2019-04-13 Added power LED to sensor board
2020-07-19 Added ground terminals
2020-07-19 Recreated rescue library
2020-07-26 poweriface: improve labeling
2020-07-26 sensor: modernize
2020-07-26 ignore board plots
2020-07-26 ignore parts cache
2020-08-06 Added old wiring diagram
2020-08-24 wiring: Added some descriptions
2020-08-24 feedback: Added switch interface board
2020-08-24 drive: Added single-motor control board
2020-08-24 Rewrote readme
2020-09-05 feedback: added separate terminal header
2020-12-01 fb: removed min clearance
2020-12-01 drive: optimized routing and power plance placement
2020-12-08 Replace power pins with mini-fit jr
2021-01-05 Replaced BAS-40 with BAS-70 to avoid peak-peak overvoltage
2021-01-10 Updated LM317L part from library
2021-01-10 Added avr-can-lib submodule
2021-01-10 Ignore build sources
2021-01-10 Added power interface test program
2021-01-10 Added build instructions for poweriface firmware
2021-01-11 Fixed link markdown
2021-01-11 Fixed more link markdown
2021-01-13 Overhauled readme and added protocol and wiring information
2021-01-13 Status reports can be received by anyone
2021-01-13 Sensor status report needs a dedicated ID
2021-01-17 Added feedback board firmware
2021-01-17 Adapted poweriface firmware to use new specs
2021-01-17 Updated CAN interface docs
2021-01-17 Cleaned up schematics and removed obsolete parts
2021-01-18 Send out status after firing a relay
2021-01-18 Implement stop action
2021-01-18 Add auto-report message
2021-01-18 Implement firmware support for auto-report
2021-01-18 Add missing breaks
2021-01-18 Remove redundant rtr check
2021-01-18 Rewrite shit register contents
2021-01-18 Implement change report on feedback module
2021-01-19 Add symbolic CAN message constants
2021-01-19 Use symbolic message constants in firmware
2021-01-19 Always update last status
2021-01-19 Updated PCB layout
2021-01-20 Use bit masks for message flags
2021-01-20 Drop unused header
2021-01-24 Removed obsolete project and data sheets
2021-01-24 Replaced power board diode pad layouts
